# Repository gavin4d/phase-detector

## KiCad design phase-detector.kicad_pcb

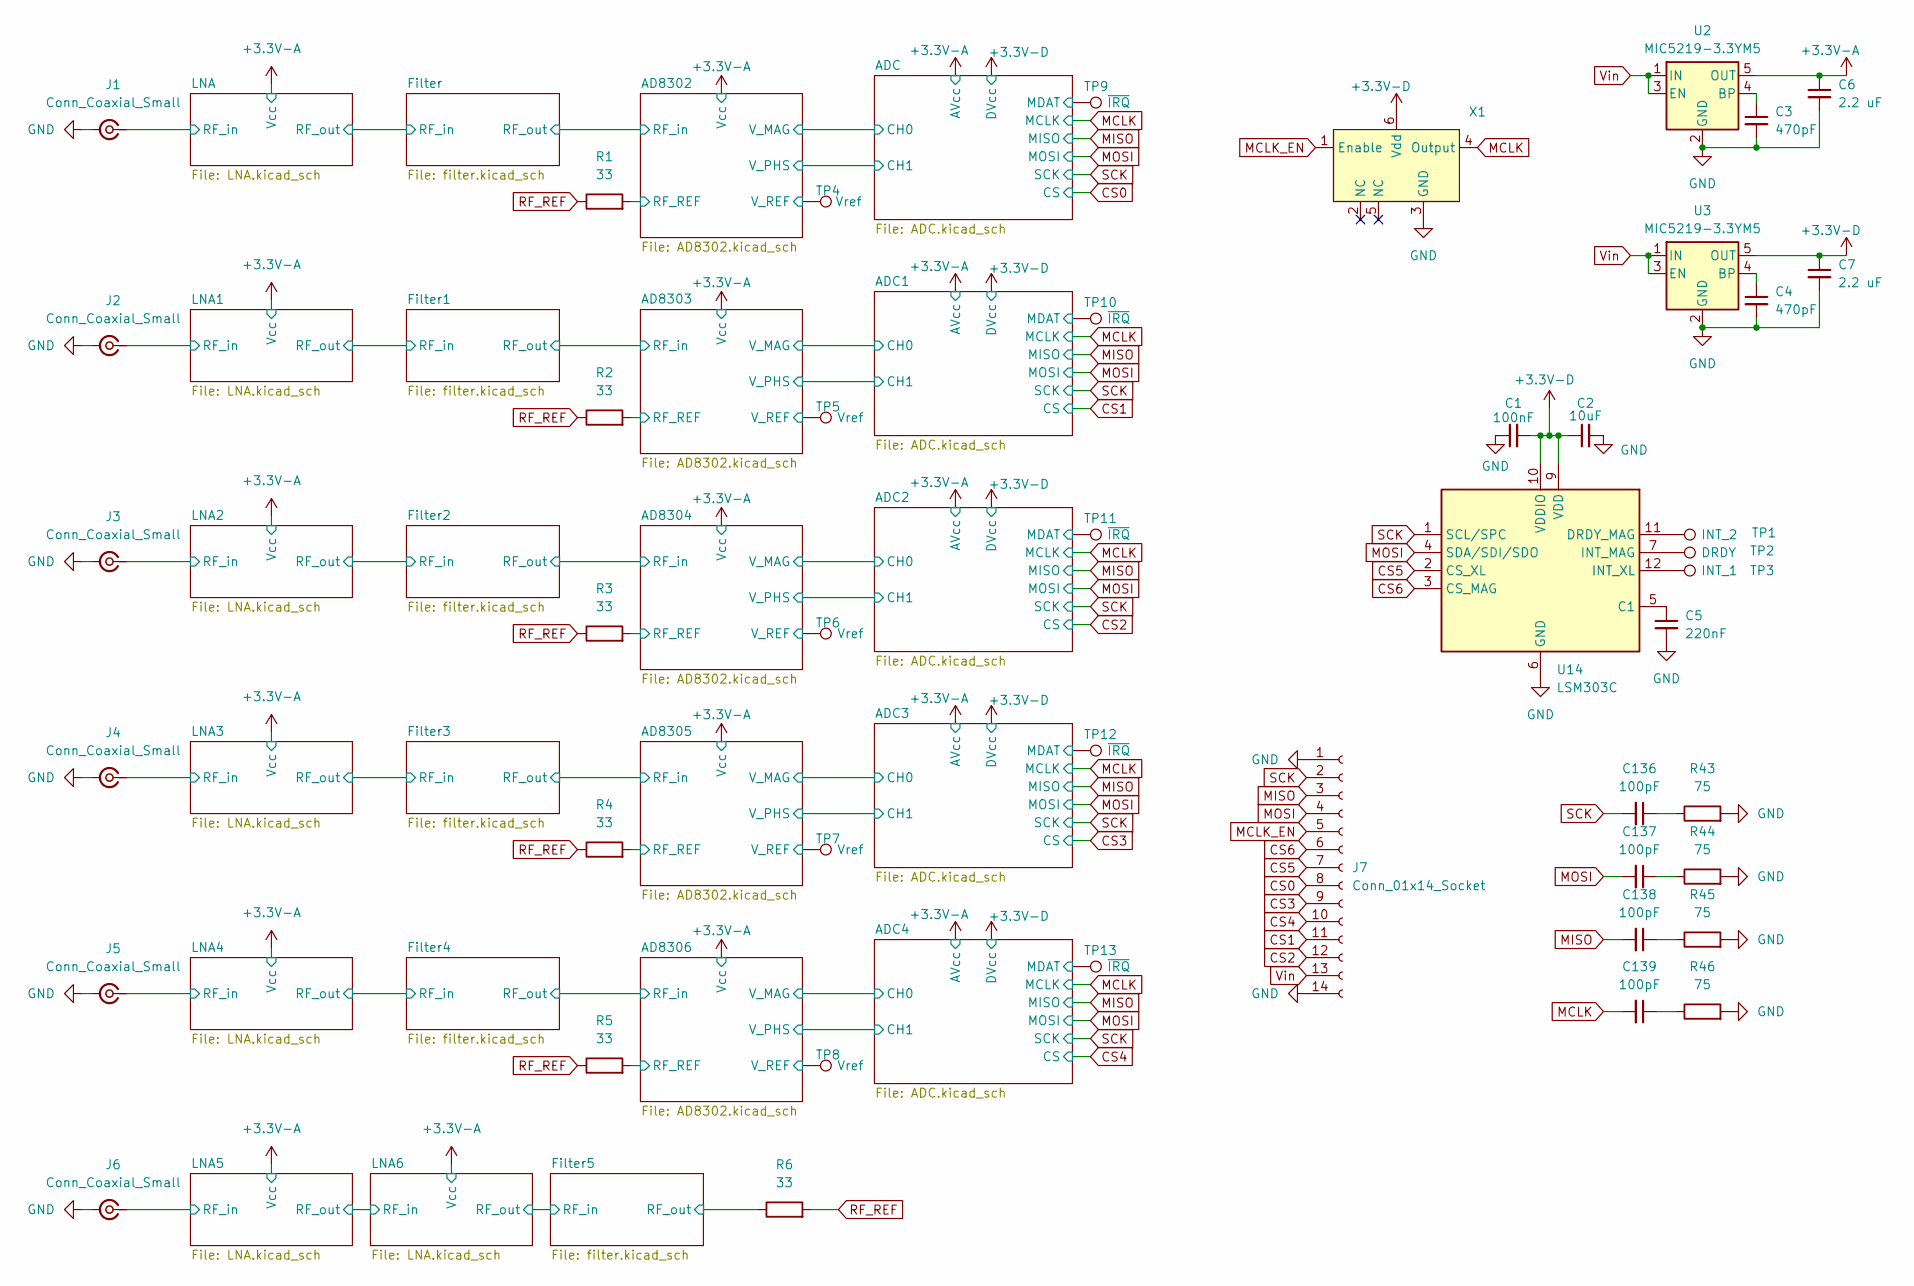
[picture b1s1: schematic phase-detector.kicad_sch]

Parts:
C1: 100nF; C_0402_1005Metric
C2: 10uF; C_0805_2012Metric
C3, C4: 470pF; C_0402_1005Metric
C5: 220nF; C_0402_1005Metric
C6, C7: 2.2 uF; C_0402_1005Metric
C136, C137, C138, C139: 100pF; C_0402_1005Metric
J1, J2, J3, J4, J5: Conn_Coaxial_Small; SMA_Amphenol_132289_EdgeMount
J6: Conn_Coaxial_Small; SMA_Amphenol_132291-12_Vertical
J7: Conn_01x14_Socket; JST_PHD_B14B-PHDSS_2x07_P2.00mm_Vertical
R1, R2, R3, R4, R5, R6: 33; R_0402_1005Metric
R43, R44, R45, R46: 75; R_0402_1005Metric
TP1: INT_2; Test_Via
TP2: DRDY; Test_Via
TP3: INT_1; Test_Via
TP4, TP5, TP6, TP7, TP8: Vref; Test_Via
TP9, TP10, TP11, TP12, TP13: ~{IRQ}; Test_Via
U2, U3: MIC5219-3.3YM5; SOT-23-5
U14: LSM303C; LGA-12_2x2mm_P0.5mm
X1: DSC1121

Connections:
+3.3V-A: C6.1, U2.5 (OUT); also elsewhere on the board
+3.3V-D: C1.2, C2.1, C7.1, U3.5 (OUT), U14.9 (VDD), U14.10 (VDDIO), X1.6 (Vdd); also elsewhere on the board
/AD8302/RF_REF: R1.2; also elsewhere on the board
/AD8302/V_REF: TP4.1; also elsewhere on the board
/AD8303/RF_REF: R2.2; also elsewhere on the board
/AD8303/V_REF: TP5.1; also elsewhere on the board
/AD8304/RF_REF: R3.2; also elsewhere on the board
/AD8304/V_REF: TP6.1; also elsewhere on the board
/AD8305/RF_REF: R4.2; also elsewhere on the board
/AD8305/V_REF: TP7.1; also elsewhere on the board
/AD8306/RF_REF: R5.2; also elsewhere on the board
/AD8306/V_REF: TP8.1; also elsewhere on the board
/ADC1/MDAT: TP10.1; also elsewhere on the board
/ADC2/MDAT: TP11.1; also elsewhere on the board
/ADC3/MDAT: TP12.1; also elsewhere on the board
/ADC4/MDAT: TP13.1; also elsewhere on the board
/ADC/MDAT: TP9.1; also elsewhere on the board
/Filter5/RF_out: R6.1; also elsewhere on the board
/LNA1/RF_in: J2.1 (In); also elsewhere on the board
/LNA2/RF_in: J3.1 (In); also elsewhere on the board
/LNA3/RF_in: J4.1 (In); also elsewhere on the board
/LNA4/RF_in: J5.1 (In); also elsewhere on the board
/LNA5/RF_in: J6.1 (In); also elsewhere on the board
/LNA/RF_in: J1.1 (In); also elsewhere on the board
CS0: J7.8; also elsewhere on the board
CS1: J7.11; also elsewhere on the board
CS2: J7.12; also elsewhere on the board
CS3: J7.9; also elsewhere on the board
CS4: J7.10; also elsewhere on the board
CS5: J7.7, U14.2 (CS_XL)
CS6: J7.6, U14.3 (CS_MAG)
GND: C1.1, C2.2, C3.2, C4.2, C5.2, C6.2, C7.2, J1.2 (Ext), J2.2 (Ext), J3.2 (Ext), J4.2 (Ext), J5.2 (Ext), J6.2 (Ext), J7.1, J7.14, R43.2, R44.2, R45.2, R46.2, U2.2 (GND), U3.2 (GND), U14.6 (GND), U14.8 (GND), X1.3 (GND); also elsewhere on the board
MCLK: C139.2, X1.4 (Output); also elsewhere on the board
MCLK_EN: J7.5, X1.1 (Enable)
MISO: C138.2, J7.3; also elsewhere on the board
MOSI: C137.2, J7.4, U14.4 (SDA/SDI/SDO); also elsewhere on the board
unnamed: C136.1, R43.1
unnamed: C137.1, R44.1
unnamed: C138.1, R45.1
unnamed: C139.1, R46.1
unnamed: C3.1, U2.4 (BP)
unnamed: C4.1, U3.4 (BP)
unnamed: C5.1, U14.5 (C1)
unnamed: TP1.1, U14.11 (DRDY_MAG)
unnamed: TP2.1, U14.7 (INT_MAG)
unnamed: TP3.1, U14.12 (INT_XL)
RF_REF: R1.1, R2.1, R3.1, R4.1, R5.1, R6.2
SCK: C136.2, J7.2, U14.1 (SCL/SPC); also elsewhere on the board
Vin: J7.13, U2.1 (IN), U2.3 (EN), U3.1 (IN), U3.3 (EN)

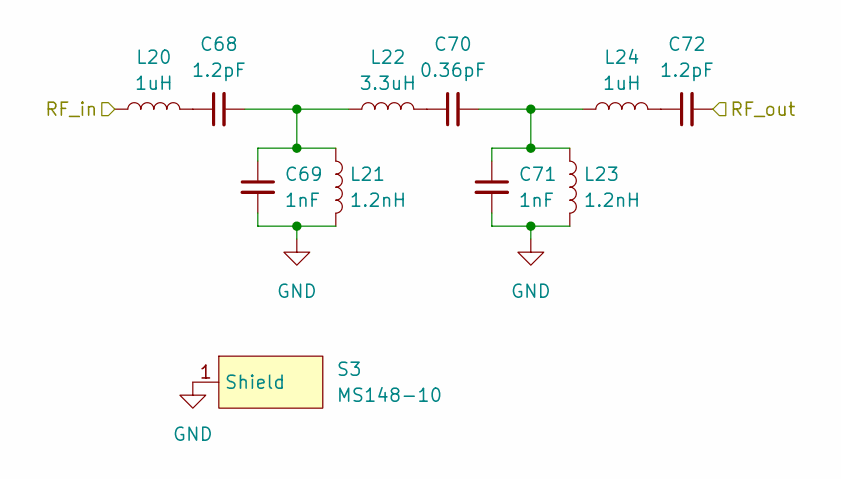
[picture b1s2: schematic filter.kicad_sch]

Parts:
C68, C72: 1.2pF; C_0402_1005Metric
C69, C71: 1nF; C_0402_1005Metric
C70: 0.36pF; C_0402_1005Metric
L20, L24: 1uH; L_0402_1005Metric
L21, L23: 1.2nH; L_0402_1005Metric
L22: 3.3uH; L_0402_1005Metric
S3: MS148-10

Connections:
/AD8304/RF_in: C72.2; also elsewhere on the board
/Filter2/RF_in: L20.1; also elsewhere on the board
GND: C69.2, C71.2, L21.2, L23.2, S3.1 (Shield); also elsewhere on the board
unnamed: C68.1, L20.2
unnamed: C68.2, C69.1, L21.1, L22.1
unnamed: C70.1, L22.2
unnamed: C70.2, C71.1, L23.1, L24.1
unnamed: C72.1, L24.2

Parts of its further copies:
C12, C16, C45, C49, C105, C109, C110, C114, C123, C127: 1.2pF; C_0402_1005Metric
C13, C15, C46, C48, C106, C108, C111, C113, C124, C126: 1nF; C_0402_1005Metric
C14, C47, C107, C112, C125: 0.36pF; C_0402_1005Metric
L4, L8, L11, L15, L30, L34, L35, L39, L46, L50: 1uH; L_0402_1005Metric
L5, L7, L12, L14, L31, L33, L36, L38, L47, L49: 1.2nH; L_0402_1005Metric
L6, L13, L32, L37, L48: 3.3uH; L_0402_1005Metric
S1, S2, S4, S5, S6: MS148-10

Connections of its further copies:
/AD8302/RF_in: C16.2; also elsewhere on the board
/AD8303/RF_in: C49.2; also elsewhere on the board
/AD8305/RF_in: C109.2; also elsewhere on the board
/AD8306/RF_in: C114.2; also elsewhere on the board
/Filter1/RF_in: L11.1; also elsewhere on the board
/Filter3/RF_in: L30.1; also elsewhere on the board
/Filter4/RF_in: L35.1; also elsewhere on the board
/Filter5/RF_in: L46.1; also elsewhere on the board
/Filter5/RF_out: C127.2; also elsewhere on the board
/Filter/RF_in: L4.1; also elsewhere on the board
GND: C13.2, C15.2, C46.2, C48.2, C106.2, C108.2, C111.2, C113.2, C124.2, C126.2, L5.2, L7.2, L12.2, L14.2, L31.2, L33.2, L36.2, L38.2, L47.2, L49.2, S1.1 (Shield), S2.1 (Shield), S4.1 (Shield), S5.1 (Shield), S6.1 (Shield); also elsewhere on the board
unnamed: C12.1, L4.2
unnamed: C12.2, C13.1, L5.1, L6.1
unnamed: C14.1, L6.2
unnamed: C14.2, C15.1, L7.1, L8.1
unnamed: C16.1, L8.2
unnamed: C45.1, L11.2
unnamed: C45.2, C46.1, L12.1, L13.1
unnamed: C47.1, L13.2
unnamed: C47.2, C48.1, L14.1, L15.1
unnamed: C49.1, L15.2
unnamed: C105.1, L30.2
unnamed: C105.2, C106.1, L31.1, L32.1
unnamed: C107.1, L32.2
unnamed: C107.2, C108.1, L33.1, L34.1
unnamed: C109.1, L34.2
unnamed: C110.1, L35.2
unnamed: C110.2, C111.1, L36.1, L37.1
unnamed: C112.1, L37.2
unnamed: C112.2, C113.1, L38.1, L39.1
unnamed: C114.1, L39.2
unnamed: C123.1, L46.2
unnamed: C123.2, C124.1, L47.1, L48.1
unnamed: C125.1, L48.2
unnamed: C125.2, C126.1, L49.1, L50.1
unnamed: C127.1, L50.2

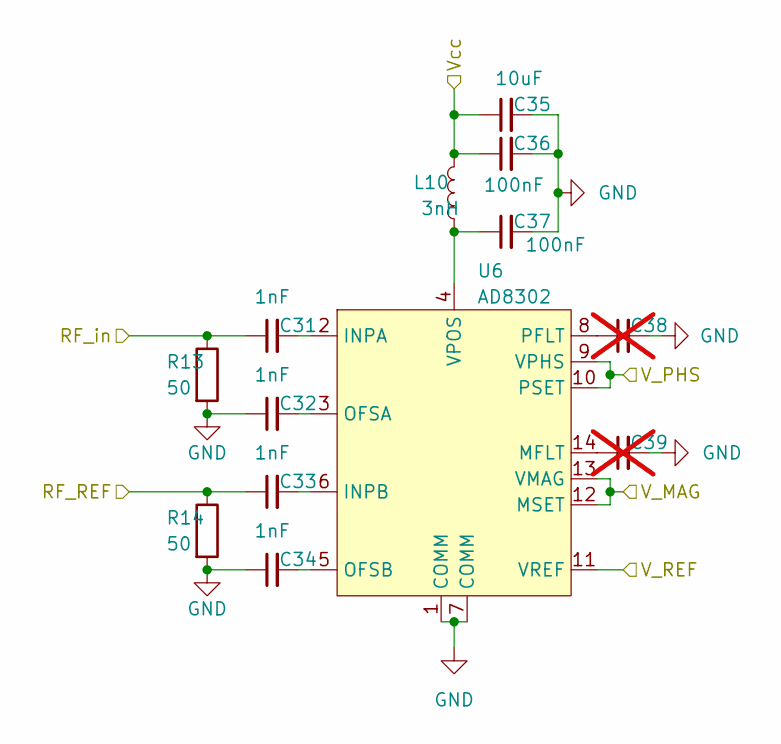
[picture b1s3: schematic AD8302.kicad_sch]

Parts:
C31, C32, C33, C34: 1nF; C_0402_1005Metric
C35: 10uF; C_0402_1005Metric
C36, C37: 100nF; C_0402_1005Metric
C38, C39: C_0402_1005Metric; not fitted
L10: 3nH; L_0402_1005Metric
R13, R14: 50; R_0402_1005Metric
U6: AD8302; TSSOP-14_4.4x5mm_P0.65mm

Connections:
+3.3V-A: C35.1, C36.1, L10.2; also elsewhere on the board
/AD8303/RF_REF: C33.1, R14.1; also elsewhere on the board
/AD8303/RF_in: C31.1, R13.1; also elsewhere on the board
/AD8303/V_MAG: U6.12 (MSET), U6.13 (VMAG); also elsewhere on the board
/AD8303/V_PHS: U6.9 (VPHS), U6.10 (PSET); also elsewhere on the board
/AD8303/V_REF: U6.11 (VREF); also elsewhere on the board
GND: C32.1, C34.1, C35.2, C36.2, C37.2, C38.2, C39.2, R13.2, R14.2, U6.1 (COMM), U6.7 (COMM); also elsewhere on the board
unnamed: C31.2, U6.2 (INPA)
unnamed: C33.2, U6.6 (INPB)
unnamed: C39.1, U6.14 (MFLT)
unnamed: C32.2, U6.3 (OFSA)
unnamed: C34.2, U6.5 (OFSB)
unnamed: C38.1, U6.8 (PFLT)
unnamed: C37.1, L10.1, U6.4 (VPOS)

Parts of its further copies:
C17, C18, C19, C20, C54, C55, C56, C57, C77, C78, C79, C80, C86, C87, C88, C89: 1nF; C_0402_1005Metric
C21, C58, C81, C90: 10uF; C_0402_1005Metric
C22, C23, C59, C60, C82, C83, C91, C92: 100nF; C_0402_1005Metric
C24, C25, C61, C62, C84, C85, C93, C94: C_0402_1005Metric; not fitted
L9, L19, L28, L29: 3nH; L_0402_1005Metric
R10, R11, R19, R20, R25, R26, R27, R28: 50; R_0402_1005Metric
U4, U8, U10, U11: AD8302; TSSOP-14_4.4x5mm_P0.65mm

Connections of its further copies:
+3.3V-A: C21.1, C22.1, C58.1, C59.1, C81.1, C82.1, C90.1, C91.1, L9.2, L19.2, L28.2, L29.2; also elsewhere on the board
/AD8302/RF_REF: C19.1, R11.1; also elsewhere on the board
/AD8302/RF_in: C17.1, R10.1; also elsewhere on the board
/AD8302/V_MAG: U4.12 (MSET), U4.13 (VMAG); also elsewhere on the board
/AD8302/V_PHS: U4.9 (VPHS), U4.10 (PSET); also elsewhere on the board
/AD8302/V_REF: U4.11 (VREF); also elsewhere on the board
/AD8304/RF_REF: C56.1, R20.1; also elsewhere on the board
/AD8304/RF_in: C54.1, R19.1; also elsewhere on the board
/AD8304/V_MAG: U8.12 (MSET), U8.13 (VMAG); also elsewhere on the board
/AD8304/V_PHS: U8.9 (VPHS), U8.10 (PSET); also elsewhere on the board
/AD8304/V_REF: U8.11 (VREF); also elsewhere on the board
/AD8305/RF_REF: C79.1, R26.1; also elsewhere on the board
/AD8305/RF_in: C77.1, R25.1; also elsewhere on the board
/AD8305/V_MAG: U10.12 (MSET), U10.13 (VMAG); also elsewhere on the board
/AD8305/V_PHS: U10.9 (VPHS), U10.10 (PSET); also elsewhere on the board
/AD8305/V_REF: U10.11 (VREF); also elsewhere on the board
/AD8306/RF_REF: C88.1, R28.1; also elsewhere on the board
/AD8306/RF_in: C86.1, R27.1; also elsewhere on the board
/AD8306/V_MAG: U11.12 (MSET), U11.13 (VMAG); also elsewhere on the board
/AD8306/V_PHS: U11.9 (VPHS), U11.10 (PSET); also elsewhere on the board
/AD8306/V_REF: U11.11 (VREF); also elsewhere on the board
GND: C18.1, C20.1, C21.2, C22.2, C23.2, C24.2, C25.2, C55.1, C57.1, C58.2, C59.2, C60.2, C61.2, C62.2, C78.1, C80.1, C81.2, C82.2, C83.2, C84.2, C85.2, C87.1, C89.1, C90.2, C91.2, C92.2, C93.2, C94.2, R10.2, R11.2, R19.2, R20.2, R25.2, R26.2, R27.2, R28.2, U4.1 (COMM), U4.7 (COMM), U8.1 (COMM), U8.7 (COMM), U10.1 (COMM), U10.7 (COMM), U11.1 (COMM), U11.7 (COMM); also elsewhere on the board
unnamed: C17.2, U4.2 (INPA)
unnamed: C19.2, U4.6 (INPB)
unnamed: C25.1, U4.14 (MFLT)
unnamed: C18.2, U4.3 (OFSA)
unnamed: C20.2, U4.5 (OFSB)
unnamed: C24.1, U4.8 (PFLT)
unnamed: C23.1, L9.1, U4.4 (VPOS)
unnamed: C54.2, U8.2 (INPA)
unnamed: C56.2, U8.6 (INPB)
unnamed: C62.1, U8.14 (MFLT)
unnamed: C55.2, U8.3 (OFSA)
unnamed: C57.2, U8.5 (OFSB)
unnamed: C61.1, U8.8 (PFLT)
unnamed: C60.1, L19.1, U8.4 (VPOS)
unnamed: C77.2, U10.2 (INPA)
unnamed: C79.2, U10.6 (INPB)
unnamed: C85.1, U10.14 (MFLT)
unnamed: C78.2, U10.3 (OFSA)
unnamed: C80.2, U10.5 (OFSB)
unnamed: C84.1, U10.8 (PFLT)
unnamed: C83.1, L28.1, U10.4 (VPOS)
unnamed: C86.2, U11.2 (INPA)
unnamed: C88.2, U11.6 (INPB)
unnamed: C94.1, U11.14 (MFLT)
unnamed: C87.2, U11.3 (OFSA)
unnamed: C89.2, U11.5 (OFSB)
unnamed: C93.1, U11.8 (PFLT)
unnamed: C92.1, L29.1, U11.4 (VPOS)

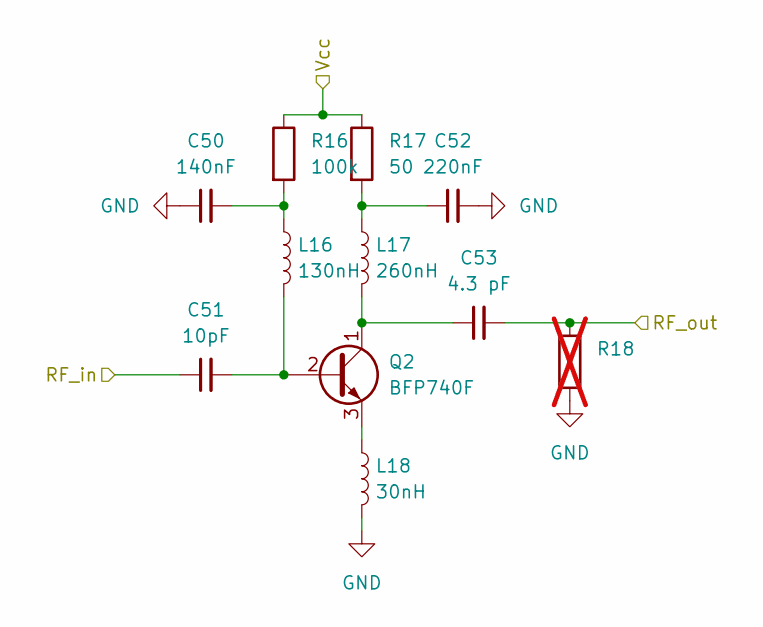
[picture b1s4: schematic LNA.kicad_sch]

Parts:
C50: 140nF; C_0402_1005Metric
C51: 10pF; C_0402_1005Metric
C52: 220nF; C_0402_1005Metric
C53: 4.3 pF; C_0402_1005Metric
L16: 130nH; L_0402_1005Metric
L17: 260nH; L_0402_1005Metric
L18: 30nH; L_0402_1005Metric
Q2: BFP740F; TSFP-4-1
R16: 100k; R_0402_1005Metric
R17: 50; R_0402_1005Metric
R18: R_0402_1005Metric; not fitted

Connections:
+3.3V-A: R16.1, R17.1; also elsewhere on the board
/Filter1/RF_in: C53.2, R18.1; also elsewhere on the board
/LNA1/RF_in: C51.1; also elsewhere on the board
GND: C50.1, C52.2, L18.2, R18.2; also elsewhere on the board
unnamed: C50.2, L16.1, R16.2
unnamed: C52.1, L17.1, R17.2
unnamed: C51.2, L16.2, Q2.2 (B)
unnamed: C53.1, L17.2, Q2.1 (C)
unnamed: L18.1, Q2.3 (E)

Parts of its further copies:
C8, C73, C115, C119, C128, C132: 140nF; C_0402_1005Metric
C9, C74, C116, C120, C129, C133: 10pF; C_0402_1005Metric
C10, C75, C117, C121, C130, C134: 220nF; C_0402_1005Metric
C11, C76, C118, C122, C131, C135: 4.3 pF; C_0402_1005Metric
L1, L25, L40, L43, L51, L54: 130nH; L_0402_1005Metric
L2, L26, L41, L44, L52, L55: 260nH; L_0402_1005Metric
L3, L27, L42, L45, L53, L56: 30nH; L_0402_1005Metric
Q1, Q3, Q4, Q5, Q6, Q7: BFP740F; TSFP-4-1
R7, R22, R31, R34, R37, R40: 100k; R_0402_1005Metric
R8, R23, R32, R35, R38, R41: 50; R_0402_1005Metric
R9, R24, R33, R36, R39, R42: R_0402_1005Metric; not fitted

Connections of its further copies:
+3.3V-A: R7.1, R8.1, R22.1, R23.1, R31.1, R32.1, R34.1, R35.1, R37.1, R38.1, R40.1, R41.1; also elsewhere on the board
/Filter2/RF_in: C76.2, R24.1; also elsewhere on the board
/Filter3/RF_in: C118.2, R33.1; also elsewhere on the board
/Filter4/RF_in: C122.2, R36.1; also elsewhere on the board
/Filter5/RF_in: C135.2, R42.1; also elsewhere on the board
/Filter/RF_in: C11.2, R9.1; also elsewhere on the board
/LNA2/RF_in: C74.1; also elsewhere on the board
/LNA3/RF_in: C116.1; also elsewhere on the board
/LNA4/RF_in: C120.1; also elsewhere on the board
/LNA5/RF_in: C129.1; also elsewhere on the board
/LNA5/RF_out: C131.2, C133.1, R39.1
/LNA/RF_in: C9.1; also elsewhere on the board
GND: C8.1, C10.2, C73.1, C75.2, C115.1, C117.2, C119.1, C121.2, C128.1, C130.2, C132.1, C134.2, L3.2, L27.2, L42.2, L45.2, L53.2, L56.2, R9.2, R24.2, R33.2, R36.2, R39.2, R42.2; also elsewhere on the board
unnamed: C8.2, L1.1, R7.2
unnamed: C10.1, L2.1, R8.2
unnamed: C73.2, L25.1, R22.2
unnamed: C75.1, L26.1, R23.2
unnamed: C115.2, L40.1, R31.2
unnamed: C117.1, L41.1, R32.2
unnamed: C119.2, L43.1, R34.2
unnamed: C121.1, L44.1, R35.2
unnamed: C128.2, L51.1, R37.2
unnamed: C130.1, L52.1, R38.2
unnamed: C132.2, L54.1, R40.2
unnamed: C134.1, L55.1, R41.2
unnamed: C9.2, L1.2, Q1.2 (B)
unnamed: C11.1, L2.2, Q1.1 (C)
unnamed: L3.1, Q1.3 (E)
unnamed: C74.2, L25.2, Q3.2 (B)
unnamed: C76.1, L26.2, Q3.1 (C)
unnamed: L27.1, Q3.3 (E)
unnamed: C116.2, L40.2, Q4.2 (B)
unnamed: C118.1, L41.2, Q4.1 (C)
unnamed: L42.1, Q4.3 (E)
unnamed: C120.2, L43.2, Q5.2 (B)
unnamed: C122.1, L44.2, Q5.1 (C)
unnamed: L45.1, Q5.3 (E)
unnamed: C129.2, L51.2, Q6.2 (B)
unnamed: C131.1, L52.2, Q6.1 (C)
unnamed: L53.1, Q6.3 (E)
unnamed: C133.2, L54.2, Q7.2 (B)
unnamed: C135.1, L55.2, Q7.1 (C)
unnamed: L56.1, Q7.3 (E)

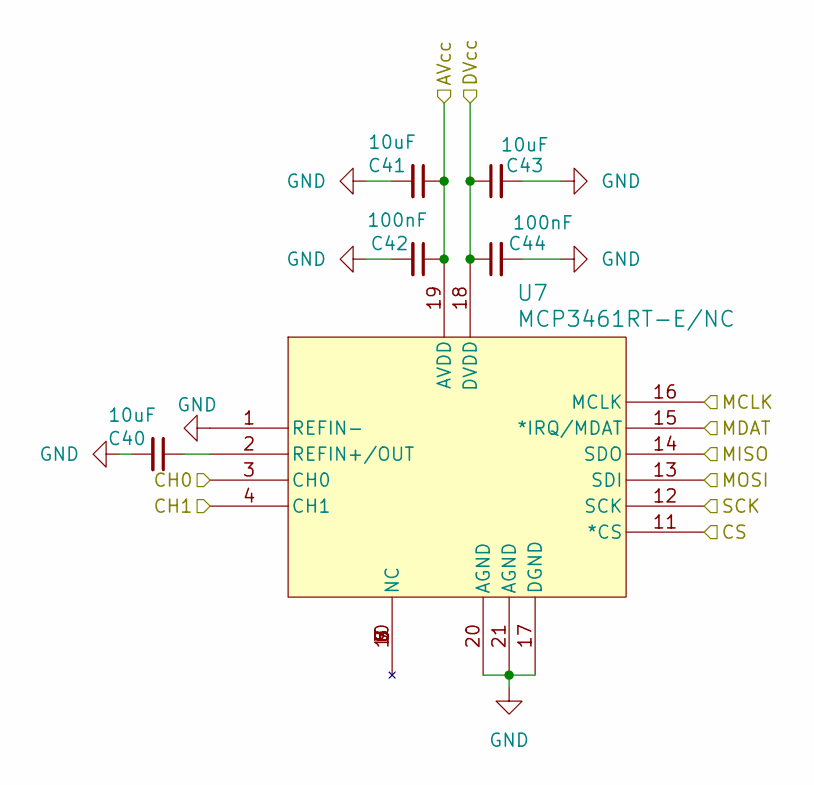
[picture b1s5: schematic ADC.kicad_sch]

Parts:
C40: 10uF; C_0402_1005Metric
C41, C43: 10uF; C_0805_2012Metric
C42, C44: 100nF; C_0402_1005Metric
U7: MCP3461RT-E/NC; UQFN-20-1EP_3x3mm_P0.4mm_EP1.85x1.85mm

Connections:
+3.3V-A: C41.1, C42.1, U7.19 (AVDD); also elsewhere on the board
+3.3V-D: C43.1, C44.1, U7.18 (DVDD); also elsewhere on the board
/AD8303/V_MAG: U7.3 (CH0); also elsewhere on the board
/AD8303/V_PHS: U7.4 (CH1); also elsewhere on the board
/ADC1/MDAT: U7.15 (*IRQ/MDAT); also elsewhere on the board
CS1: U7.11 (*CS); also elsewhere on the board
GND: C40.2, C41.2, C42.2, C43.2, C44.2, U7.1 (REFIN-), U7.17 (DGND), U7.20 (AGND), U7.21 (AGND); also elsewhere on the board
MCLK: U7.16 (MCLK); also elsewhere on the board
MISO: U7.14 (SDO); also elsewhere on the board
MOSI: U7.13 (SDI); also elsewhere on the board
unnamed: C40.1, U7.2 (REFIN+/OUT)
SCK: U7.12 (SCK); also elsewhere on the board

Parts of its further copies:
C26, C63, C95, C100: 10uF; C_0402_1005Metric
C27, C29, C64, C66, C96, C98, C101, C103: 10uF; C_0805_2012Metric
C28, C30, C65, C67, C97, C99, C102, C104: 100nF; C_0402_1005Metric
U5, U9, U12, U13: MCP3461RT-E/NC; UQFN-20-1EP_3x3mm_P0.4mm_EP1.85x1.85mm

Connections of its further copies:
+3.3V-A: C27.1, C28.1, C64.1, C65.1, C96.1, C97.1, C101.1, C102.1, U5.19 (AVDD), U9.19 (AVDD), U12.19 (AVDD), U13.19 (AVDD); also elsewhere on the board
+3.3V-D: C29.1, C30.1, C66.1, C67.1, C98.1, C99.1, C103.1, C104.1, U5.18 (DVDD), U9.18 (DVDD), U12.18 (DVDD), U13.18 (DVDD); also elsewhere on the board
/AD8302/V_MAG: U5.3 (CH0); also elsewhere on the board
/AD8302/V_PHS: U5.4 (CH1); also elsewhere on the board
/AD8304/V_MAG: U9.3 (CH0); also elsewhere on the board
/AD8304/V_PHS: U9.4 (CH1); also elsewhere on the board
/AD8305/V_MAG: U12.3 (CH0); also elsewhere on the board
/AD8305/V_PHS: U12.4 (CH1); also elsewhere on the board
/AD8306/V_MAG: U13.3 (CH0); also elsewhere on the board
/AD8306/V_PHS: U13.4 (CH1); also elsewhere on the board
/ADC2/MDAT: U9.15 (*IRQ/MDAT); also elsewhere on the board
/ADC3/MDAT: U12.15 (*IRQ/MDAT); also elsewhere on the board
/ADC4/MDAT: U13.15 (*IRQ/MDAT); also elsewhere on the board
/ADC/MDAT: U5.15 (*IRQ/MDAT); also elsewhere on the board
CS0: U5.11 (*CS); also elsewhere on the board
CS2: U9.11 (*CS); also elsewhere on the board
CS3: U12.11 (*CS); also elsewhere on the board
CS4: U13.11 (*CS); also elsewhere on the board
GND: C26.2, C27.2, C28.2, C29.2, C30.2, C63.2, C64.2, C65.2, C66.2, C67.2, C95.2, C96.2, C97.2, C98.2, C99.2, C100.2, C101.2, C102.2, C103.2, C104.2, U5.1 (REFIN-), U5.17 (DGND), U5.20 (AGND), U5.21 (AGND), U9.1 (REFIN-), U9.17 (DGND), U9.20 (AGND), U9.21 (AGND), U12.1 (REFIN-), U12.17 (DGND), U12.20 (AGND), U12.21 (AGND), U13.1 (REFIN-), U13.17 (DGND), U13.20 (AGND), U13.21 (AGND); also elsewhere on the board
MCLK: U5.16 (MCLK), U9.16 (MCLK), U12.16 (MCLK), U13.16 (MCLK); also elsewhere on the board
MISO: U5.14 (SDO), U9.14 (SDO), U12.14 (SDO), U13.14 (SDO); also elsewhere on the board
MOSI: U5.13 (SDI), U9.13 (SDI), U12.13 (SDI), U13.13 (SDI); also elsewhere on the board
unnamed: C26.1, U5.2 (REFIN+/OUT)
unnamed: C63.1, U9.2 (REFIN+/OUT)
unnamed: C95.1, U12.2 (REFIN+/OUT)
unnamed: C100.1, U13.2 (REFIN+/OUT)
SCK: U5.12 (SCK), U9.12 (SCK), U12.12 (SCK), U13.12 (SCK); also elsewhere on the board

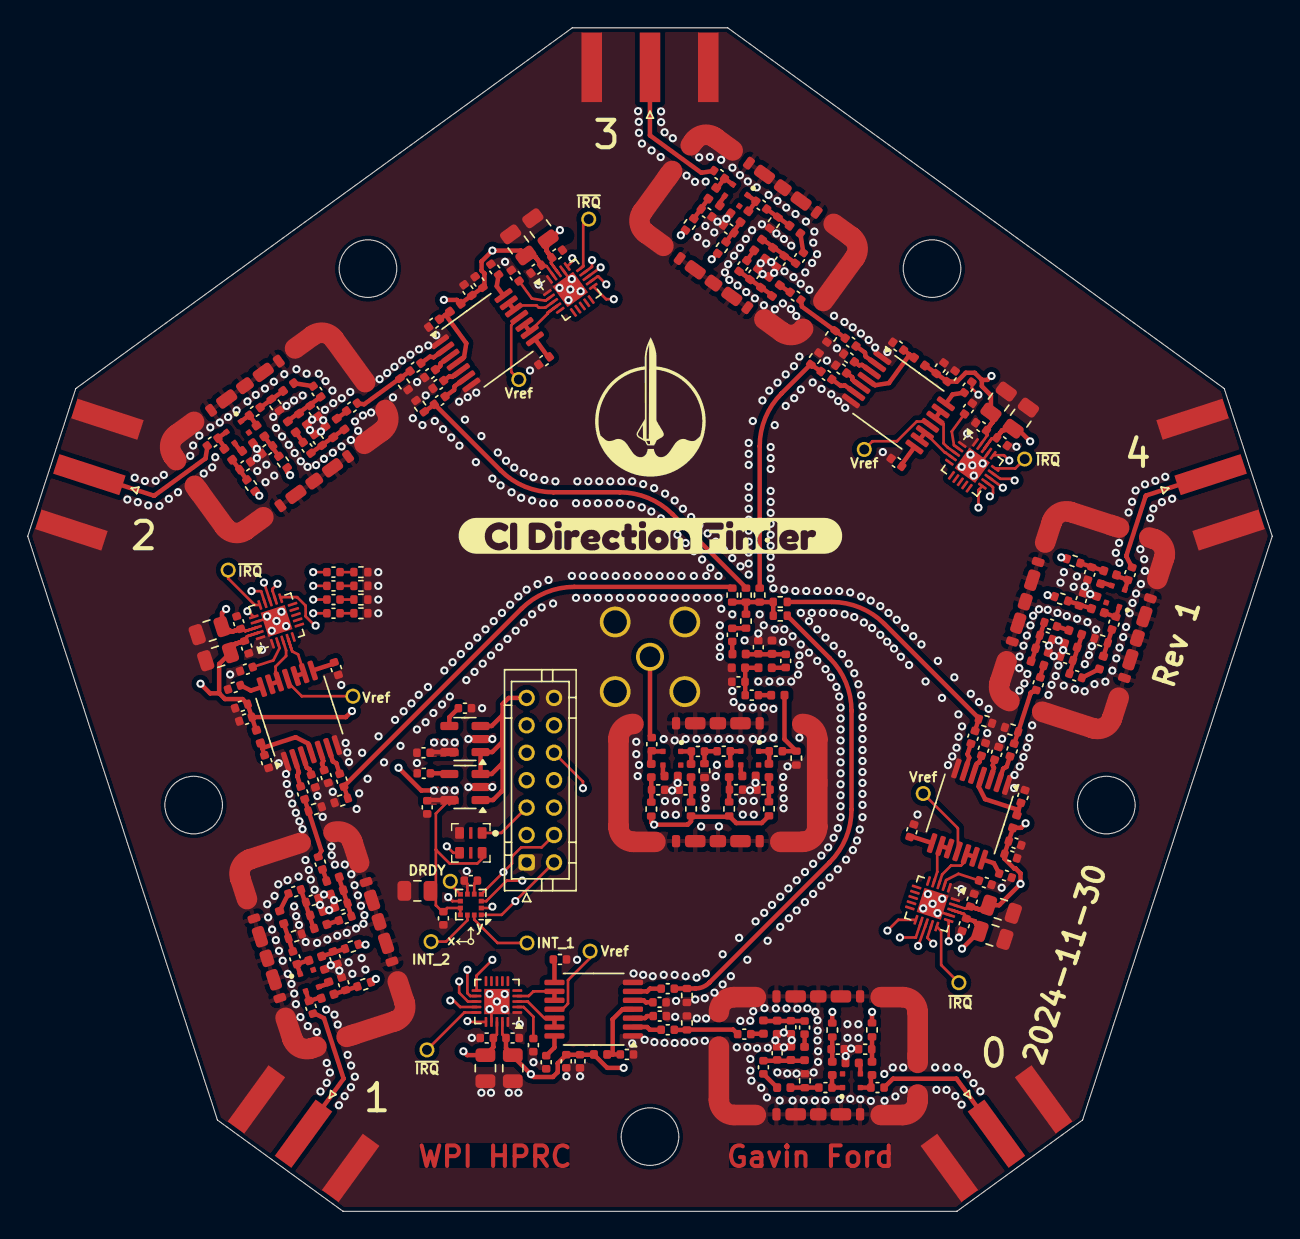
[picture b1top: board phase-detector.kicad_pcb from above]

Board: 4 copper layers, 90.8 x 86.3 mm, 284 parts (1 on the bottom side), 176 nets.

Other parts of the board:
kibuzzard-674BE006: G***; kibuzzard-674BE006

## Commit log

2024-11-29 prelim design
2024-12-01 Rev 1 ready for review
2024-12-01 added logo
2024-12-02 moon
2024-12-02 load capacitor and shield paste
2024-12-03 boards ordered
